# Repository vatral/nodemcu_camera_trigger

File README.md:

# NodeMCU camera trigger

Trigger for Pentax cameras based on sound, light and LIDAR

In extremely early development still, untested.

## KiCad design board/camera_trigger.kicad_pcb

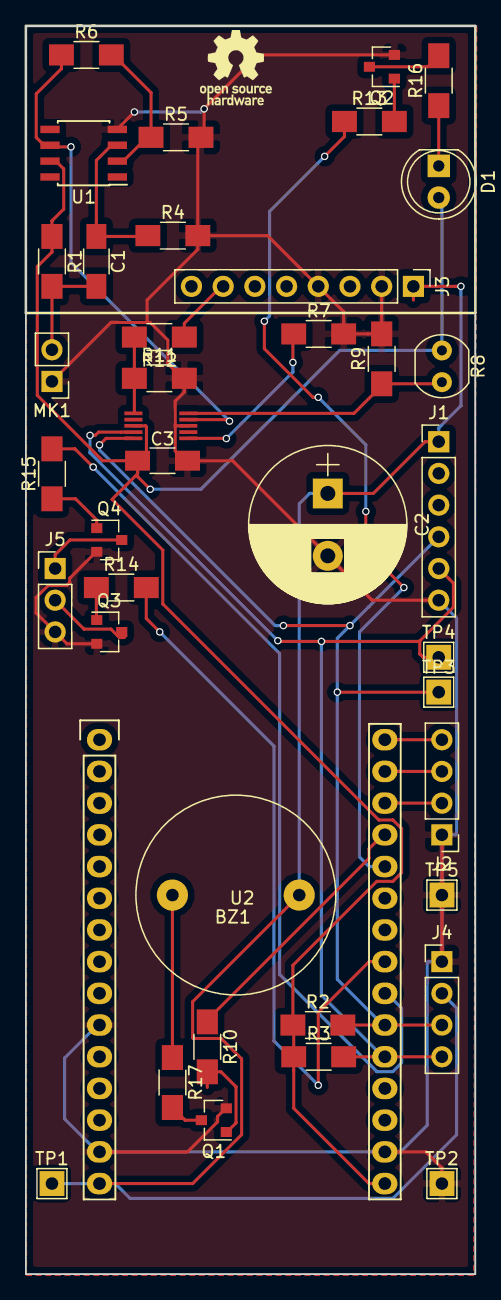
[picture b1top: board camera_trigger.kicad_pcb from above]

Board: 2 copper layers, 36.0 x 100.0 mm, 40 parts (0 on the bottom side), 30 nets.

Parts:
BZ1: Buzzer; BUZZER
C1: 0.1uF; C_1206_HandSoldering
C2: 680uF; CP_Radial_D12.5mm_P5.00mm
C3: 1uF; C_1206_HandSoldering
D1: IR204A; LED_D5.0mm
J1: LIDAR; Pin_Header_Straight_1x06_Pitch2.54mm
J2: Rotary switch; Pin_Header_Straight_1x04_Pitch2.54mm
J3: PowerBoost 1000C; Pin_Header_Straight_1x08_Pitch2.54mm
J4: Display; Pin_Header_Straight_1x04_Pitch2.54mm
J5: Audio-Jack-3; Pin_Header_Straight_1x03_Pitch2.54mm
MK1: Mic; Pin_Header_Straight_1x02_Pitch2.54mm
Q1, Q2, Q3, Q4: Q_NPN_BEC; SOT-23
R1: 2.2k; R_1206_HandSoldering
R2, R3, R9: R; R_1206_HandSoldering
R4, R6: 100k; R_1206_HandSoldering
R5, R10, R13, R14, R15: 1k; R_1206_HandSoldering
R7, R12: 10k; R_1206_HandSoldering
R8: LDR03; Resistor_LDR_4.9x4.2_RM2.54
R11: 20k; R_1206_HandSoldering
R16: 27; R_1206_HandSoldering
R17: 100; R_1206_HandSoldering
TP1, TP2, TP3, TP4, TP5: TEST; TestPoint_THTPad_2.0x2.0mm_Drill1.0mm
U1: OPA340UA; SOIC-8_3.9x4.9mm_Pitch1.27mm
U2: NodeMCU_Amica_R2
U3: ADS1115; VSSOP10

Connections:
+3V3: C3.1, D1.2, R1.1, R2.1, R3.1, R8.1, U1.7, U2.16, U3.8
+5V: BZ1.1, C2.1, J1.1, J3.1, J4.2, TP1.1, U2.15
AUD_IN: R6.1, U1.6, U3.4
AUD_OUT: R10.1, U2.27
BAT: J3.7, R12.1
FOCUS: R14.2, U2.23
GND: C2.2, C3.2, J1.6, J2.1, J3.2, J3.4, J4.1, J5.3, MK1.1, Q1.2, Q2.2, Q3.2, Q4.2, R4.2, R5.2, R7.2, R9.2, R11.2, TP2.1, TP5.1, U1.4, U2.10, U2.14, U2.17, U3.3
IR_LED: R13.1, U2.26
LDR_IN: R8.2, R9.1, U3.5
unnamed: BZ1.2, R17.1
unnamed: C1.1, R4.1, U1.3
unnamed: C1.2, MK1.2, R1.2
unnamed: D1.1, R16.1
unnamed: J5.1, Q4.3
unnamed: J5.2, Q3.3
unnamed: Q1.1, R10.2
unnamed: Q1.3, R17.2
unnamed: Q2.1, R13.2
unnamed: Q2.3, R16.2
unnamed: Q3.1, R14.1
unnamed: Q4.1, R15.1
unnamed: R5.1, R6.2, U1.2
unnamed: R7.1, U3.1
unnamed: R11.1, R12.2, U3.6
ROTARY_CLICK: J2.2, U2.28
ROTARY_NEXT: J2.4, U2.30
ROTARY_PREV: J2.3, U2.29
SCL: J1.4, J4.3, R2.2, TP3.1, U2.21, U3.10
SDA: J1.5, J4.4, R3.2, TP4.1, U2.20, U3.9
TRIG: R15.2, U2.22

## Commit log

2018-09-17 Initial version
2018-09-17 Added OSHW logo
